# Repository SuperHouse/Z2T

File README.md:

Zigbee2Tasmota Zigbee Coordinator
=================================

Combines a Wemos D1 Mini and a Z-0001 module with CC2531 CC.

Uses the Zigbee2Tasmota firmware to operate as a Zigbee Coordinator.

Features:

 * ESP8266 to run Zigbee2Tasmota
 * CC2531 Zigbee interface
 * 3D-printable case

More information is available at:

  https://www.superhouse.tv/z2t

Hardware
--------
The "Hardware" directory contains the PCB design as an EAGLE project.
EAGLE PCB design software is available from Autodesk free for
non-commercial use.

Firmware
--------
The "Firmware" directory contains example firmware as an Arduino
project.

Enclosure
---------
The "Enclosure" directory contains STLs for a case that can be
3D-printed.

The two halves of the case should be printed with the flat face down to
the printer bed.

The case can be held shut by 8mm M3 bolts.

Credits
-------
 * Jonathan Oxer <jon@oxer.com.au>

License
-------
Copyright 2020 SuperHouse Automation Pty Ltd  www.superhouse.tv  

The hardware portion of this project is licensed under the TAPR Open
Hardware License (www.tapr.org/OHL). The "license" folder within this
repository contains a copy of this license in plain text format.

The software portion of this project is licensed under the Simplified
BSD License. The "licence" folder within this project contains a
copy of this license in plain text format.

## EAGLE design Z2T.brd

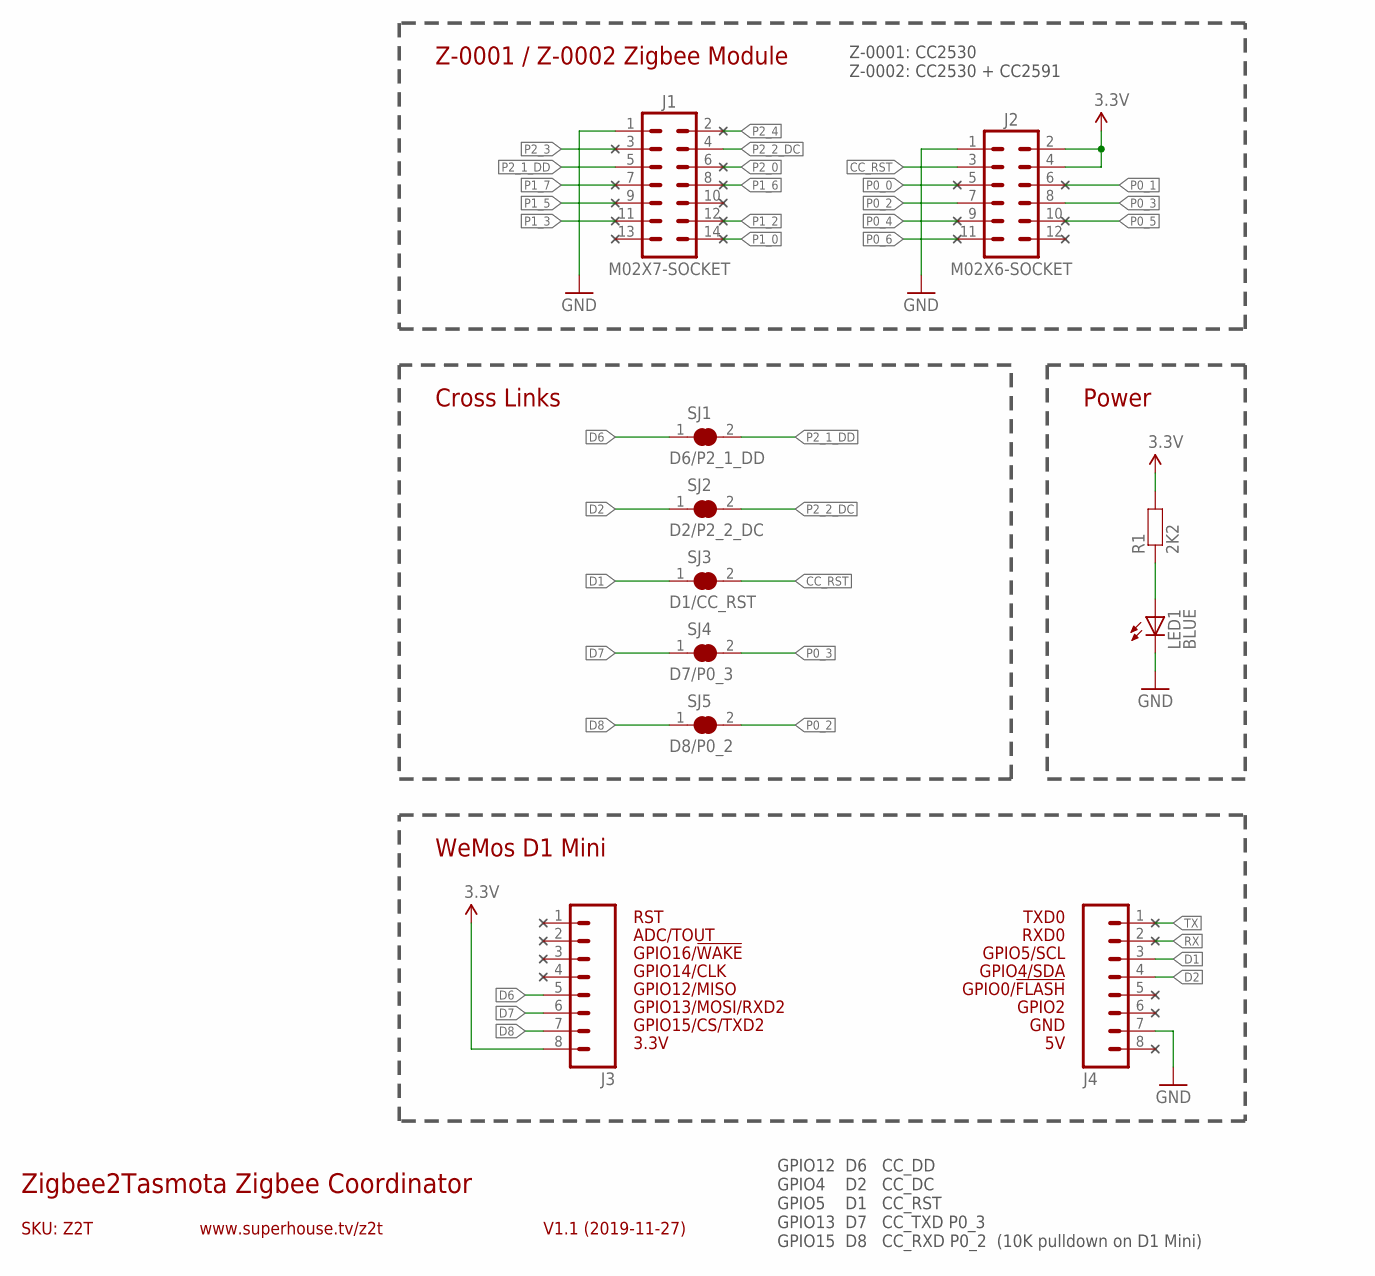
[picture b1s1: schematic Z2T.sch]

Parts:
J1: M02X7-SOCKET; 2X07-S
J2: M02X6-SOCKET; 2X06-S
J3, J4: M08; 1X08
LED1: BLUE; LED-0603
R1: 2K2; R0603
SJ1: D6/P2_1_DD; SJC
SJ2: D2/P2_2_DC; SJC
SJ3: D1/CC_RST; SJC
SJ4: D7/P0_3; SJC
SJ5: D8/P0_2; SJC

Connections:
3.3V: J2.2, J2.4, J3.8, R1.2
CC_RST: J2.3, SJ3.2
D1: J4.3, SJ3.1
D2: J4.4, SJ2.1
D6: J3.5, SJ1.1
D7: J3.6, SJ4.1
D8: J3.7, SJ5.1
GND: J1.1, J2.1, J4.7, LED1.C
unnamed: LED1.A, R1.1
P0_0: J2.5
P0_1: J2.6
P0_2: J2.7, SJ5.2
P0_3: J2.8, SJ4.2
P0_4: J2.9
P0_5: J2.10
P0_6: J2.11
P1_0: J1.14
P1_2: J1.12
P1_3: J1.11
P1_5: J1.9
P1_6: J1.8
P1_7: J1.7
P2_0: J1.6
P2_1_DD: J1.5, SJ1.2
P2_2_DC: J1.4, SJ2.2
P2_3: J1.3
P2_4: J1.2
RX: J4.2
TX: J4.1

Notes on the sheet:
GPIO2
GPIO0/!FLASH
GPIO12/MISO
GPIO4/SDA
GPIO5/SCL
RXD0
TXD0
GPIO13/MOSI/RXD2
GPIO14/CLK
GPIO15/CS/TXD2
GPIO16/!WAKE
SKU: Z2T
Zigbee2Tasmota Zigbee Coordinator
V1.1 (2019-11-27)
www.superhouse.tv/z2t
ADC/TOUT
GPIO12 D6 CC_DD GPIO4 D2 CC_DC GPIO5 D1 CC_RST GPIO13 D7 CC_TXD P0_3 GPIO15 D8 CC_RXD P0_2 (10K pulldown on D1 Mini)
GND
3.3V
RST
Cross Links
Z-0001 / Z-0002 Zigbee Module
WeMos D1 Mini
Power
Z-0001: CC2530 Z-0002: CC2530 + CC2591

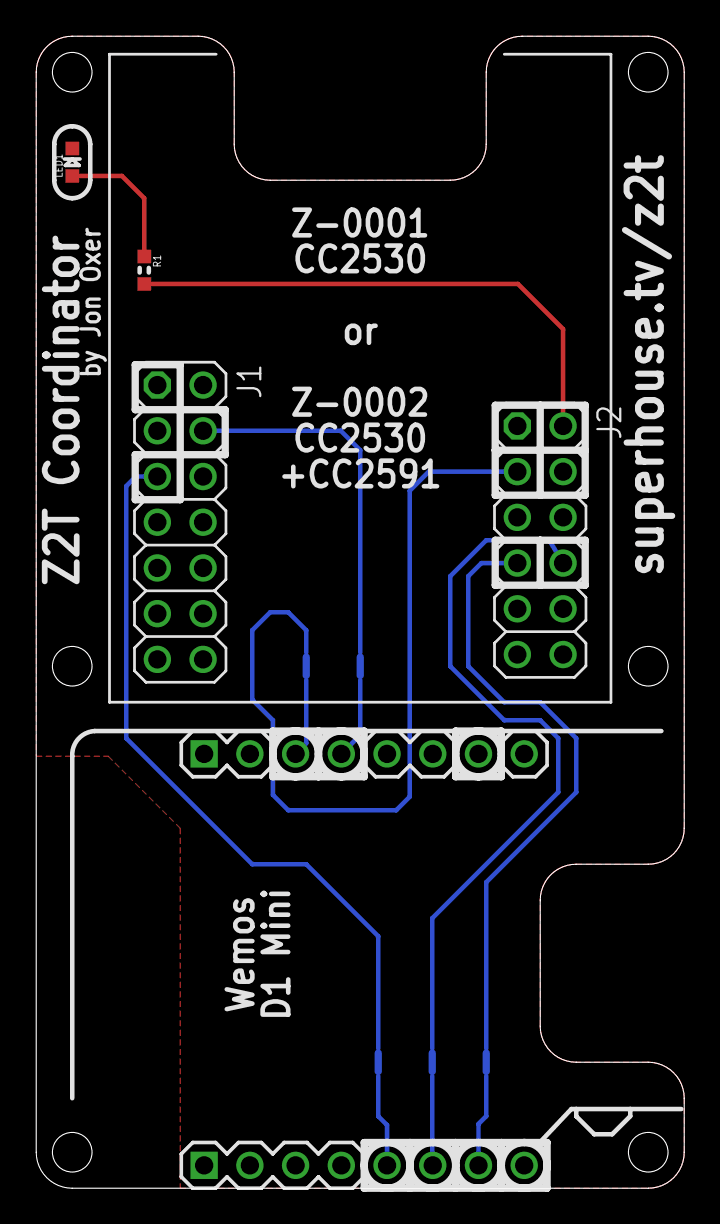
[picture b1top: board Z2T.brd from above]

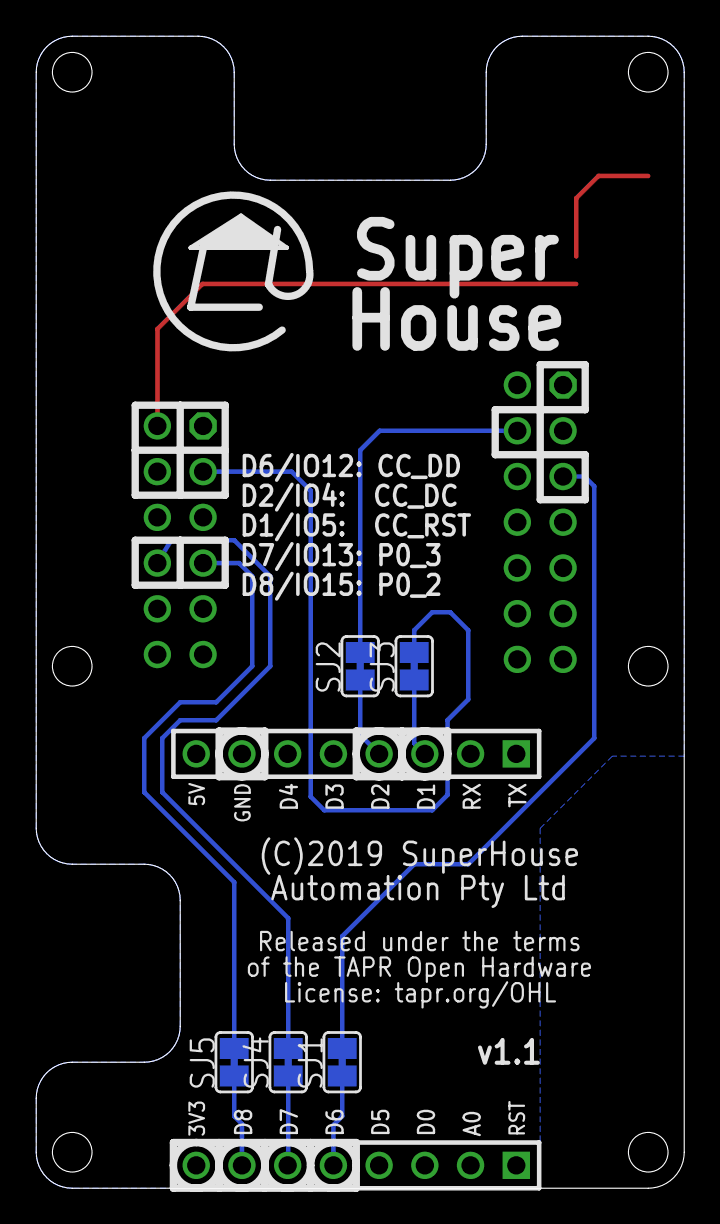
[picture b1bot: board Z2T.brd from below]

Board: 2 copper layers, 36.0 x 64.0 mm, 11 parts (5 on the bottom side), 13 nets.

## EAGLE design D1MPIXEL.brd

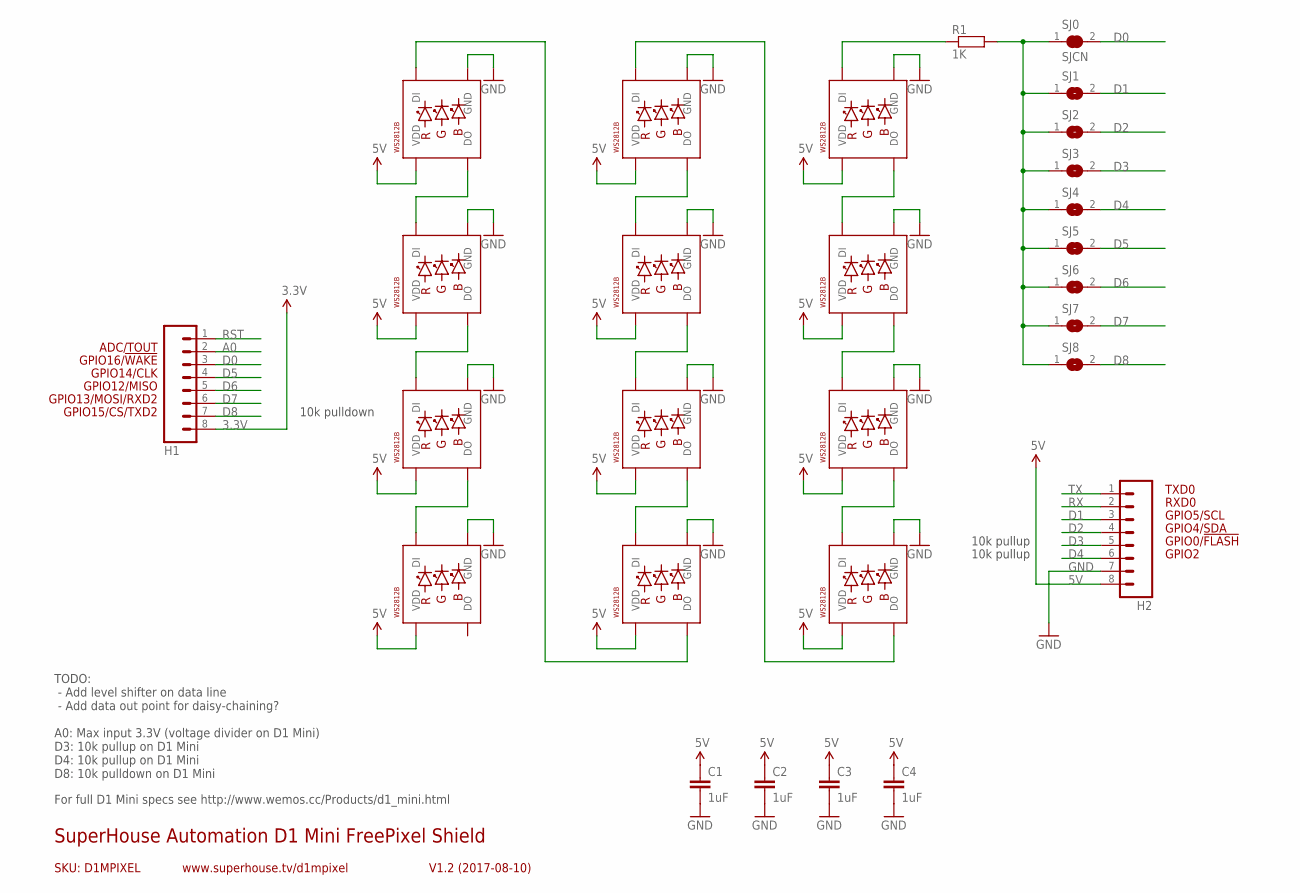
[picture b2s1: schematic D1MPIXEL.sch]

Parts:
C1, C2, C3, C4: 1uF; 0603
H1, H2: M08; 1X08
LED1, LED2, LED3, LED4, LED5, LED6, LED7, LED8, LED9, LED10, LED11, LED12: WS2812B5050; WS2812B
R1: 1K; 0603
SJ0: SJCN; SJC
SJ1, SJ2, SJ3, SJ4, SJ5, SJ6, SJ7, SJ8: SJN; SJ

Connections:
3.3V: H1.8
5V: C1.1, C2.1, C3.1, C4.1, H2.8, LED1.1-VDD (VDD), LED2.1-VDD (VDD), LED3.1-VDD (VDD), LED4.1-VDD (VDD), LED5.1-VDD (VDD), LED6.1-VDD (VDD), LED7.1-VDD (VDD), LED8.1-VDD (VDD), LED9.1-VDD (VDD), LED10.1-VDD (VDD), LED11.1-VDD (VDD), LED12.1-VDD (VDD)
A0: H1.2
D0: H1.3, SJ0.2
D1: H2.3, SJ1.2
D2: H2.4, SJ2.2
D3: H2.5, SJ3.2
D4: H2.6, SJ4.2
D5: H1.4, SJ5.2
D6: H1.5, SJ6.2
D7: H1.6, SJ7.2
D8: H1.7, SJ8.2
GND: C1.2, C2.2, C3.2, C4.2, H2.7, LED1.3-GND (GND), LED2.3-GND (GND), LED3.3-GND (GND), LED4.3-GND (GND), LED5.3-GND (GND), LED6.3-GND (GND), LED7.3-GND (GND), LED8.3-GND (GND), LED9.3-GND (GND), LED10.3-GND (GND), LED11.3-GND (GND), LED12.3-GND (GND)
unnamed: LED1.2-DOUT (DO), LED2.4-DIN (DI)
unnamed: LED2.2-DOUT (DO), LED3.4-DIN (DI)
unnamed: LED3.2-DOUT (DO), LED4.4-DIN (DI)
unnamed: LED5.2-DOUT (DO), LED6.4-DIN (DI)
unnamed: LED6.2-DOUT (DO), LED7.4-DIN (DI)
unnamed: LED7.2-DOUT (DO), LED8.4-DIN (DI)
unnamed: LED11.2-DOUT (DO), LED12.4-DIN (DI)
unnamed: LED10.2-DOUT (DO), LED11.4-DIN (DI)
unnamed: LED9.2-DOUT (DO), LED10.4-DIN (DI)
unnamed: LED4.2-DOUT (DO), LED5.4-DIN (DI)
unnamed: LED8.2-DOUT (DO), LED9.4-DIN (DI)
unnamed: R1.2, SJ0.1, SJ1.1, SJ2.1, SJ3.1, SJ4.1, SJ5.1, SJ6.1, SJ7.1, SJ8.1
unnamed: LED1.4-DIN (DI), R1.1
RST: H1.1
RX: H2.2
TX: H2.1

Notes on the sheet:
GPIO2
GPIO0/!FLASH
GPIO12/MISO
GPIO4/SDA
GPIO5/SCL
RXD0
TXD0
GPIO13/MOSI/RXD2
GPIO14/CLK
GPIO15/CS/TXD2
GPIO16/!WAKE
SKU: D1MPIXEL
SuperHouse Automation D1 Mini FreePixel Shield
V1.2 (2017-08-10)
www.superhouse.tv/d1mpixel
ADC/TOUT
TODO: - Add level shifter on data line - Add data out point for daisy-chaining? A0: Max input 3.3V (voltage divider on D1 Mini) D3: 10k pullup on D1 Mini D4: 10k pullup on D1 Mini D8: 10k pulldown on D1 Mini
10k pulldown
10k pullup
For full D1 Mini specs see http://www.wemos.cc/Products/d1_mini.html

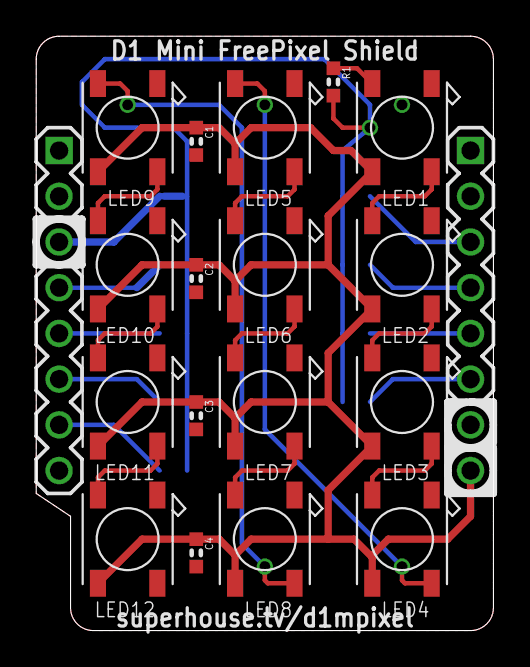
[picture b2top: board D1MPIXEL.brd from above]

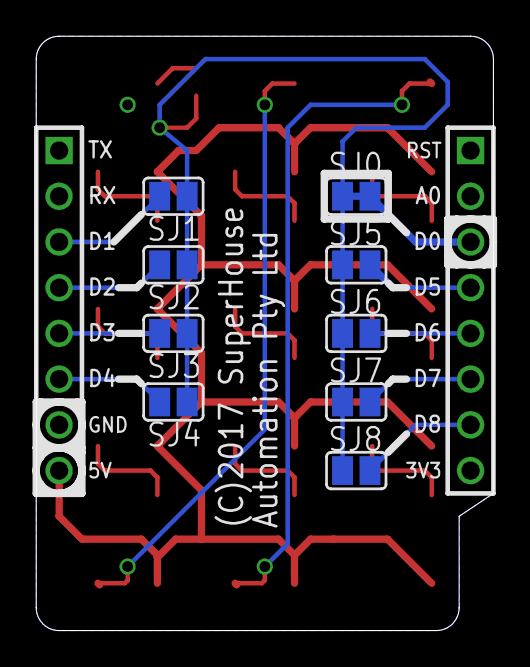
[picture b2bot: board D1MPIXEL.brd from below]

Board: 2 copper layers, 25.4 x 33.0 mm, 28 parts (9 on the bottom side), 24 nets.

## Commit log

2018-03-28 Import of project from 2017
2019-11-09 Rough position on board
2019-11-10 Mechanical adjustments on Zigbee module
2019-11-12 Final routing, silkscreen, DRC, and docs for v1.0 release
2019-11-20 Fixed spacing on Zigbee module headers
2019-11-26 Added power LED, clearance for USB socket, and pulled back copper near WiFi antenna
2019-11-26 Schematic clarification, silkscreen tweaks
2020-03-17 Final synch with Fusion 360 for v1.1 release
2020-07-06 Replaced header footprint
2020-08-13 More restructuring
2020-08-13 Added images and firmware

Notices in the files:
D1MPIXEL.brd:
(C)2017 SuperHouse
Z2T.brd:
(C)2019 SuperHouse
License: tapr.org/OHL
parts and their libraries:
freetronics-original: Licensing: CC v3.0 Share-Alike You are welcome to use this library for commercial purposes.
